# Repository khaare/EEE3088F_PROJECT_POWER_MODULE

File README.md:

# EEE3088F_PROJECT_POWER_MODULE
Our project involves designing and manufacturing the power module for the MM.  The processor, motherboard, and sensing modules have already been designed, so this directory will specifically focus on the design of four functions of the power module, which are to
handle bidirectional motor control, provide External load switching for the mm, voltage regulation and provide an ON/OFF switch for the robot

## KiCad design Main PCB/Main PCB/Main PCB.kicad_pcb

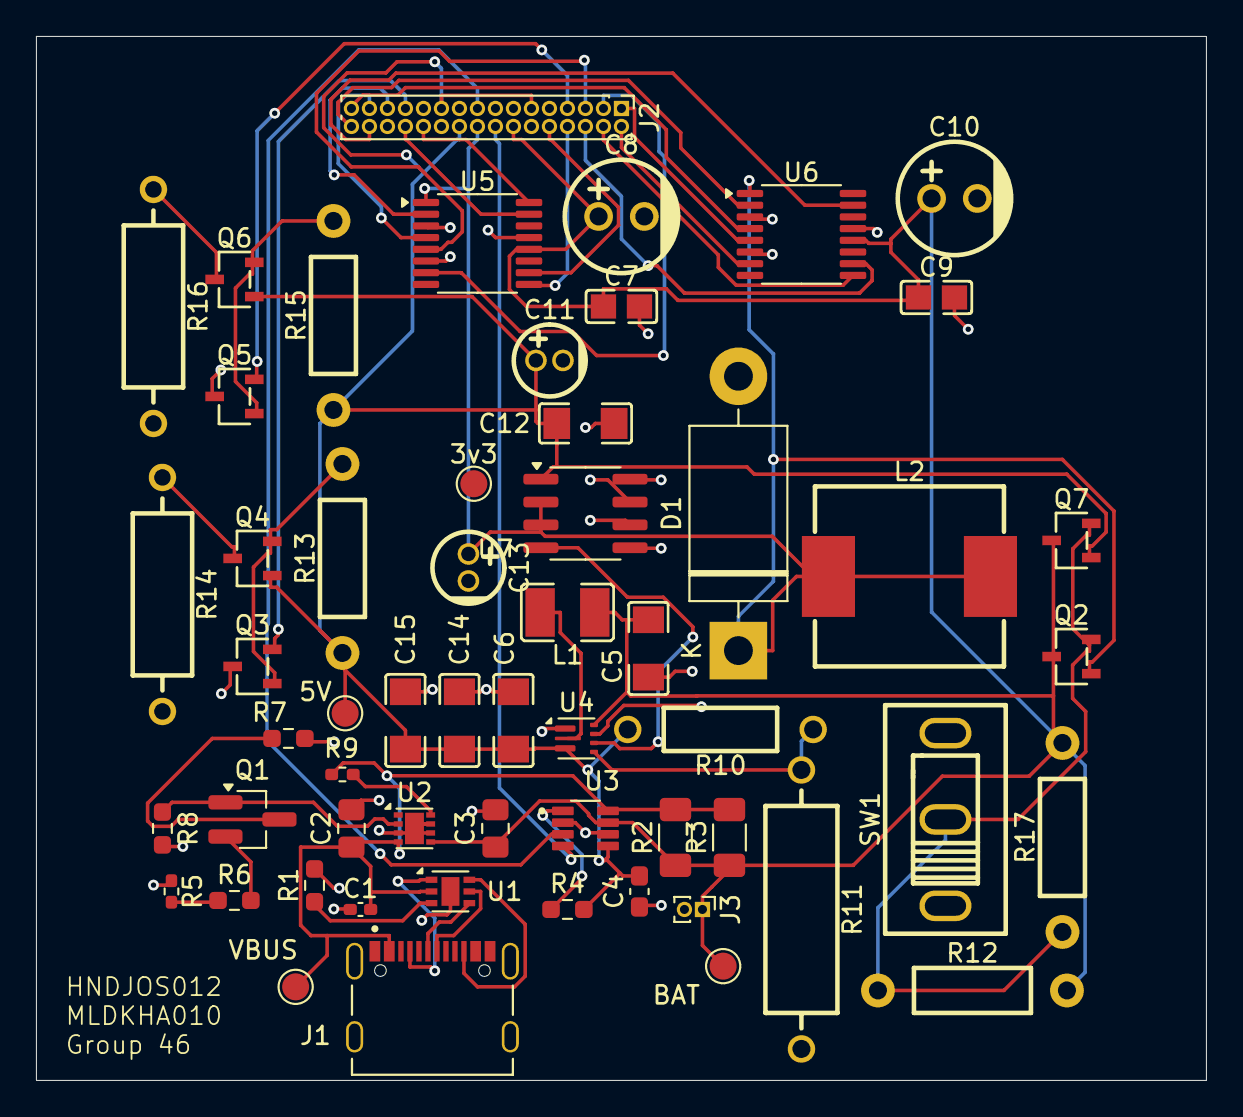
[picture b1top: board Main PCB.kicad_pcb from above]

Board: 2 copper layers, 65.0 x 58.0 mm, 57 parts (0 on the bottom side), 43 nets.

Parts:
3v3, 5V: TestPoint_Pad_D1.5mm
BAT: TestPoint_Pad_D1.5mm
C1: 1uF; C_0402_1005Metric_Pad0.74x0.62mm_HandSolder
C2, C3: 10uF; C_0805_2012Metric_Pad1.18x1.45mm_HandSolder
C4: 100n; C_0603_1608Metric_Pad1.08x0.95mm_HandSolder
C5: 10uF; C1206
C6, C14, C15: 22uF; C1206
C7, C9: 0.01uF; C0805
C8, C10: 10uF; CAP-TH_BD6.3-P2.50-D1.0-FD
C11, C13: 22uF; CAP-TH_BD4.0-P1.50-D0.8-FD
C12: 0.1uF; C1206
D1: 1N5820; D_DO-201AD_P15.24mm_Horizontal
J1: USB_C_Receptacle_USB2.0_16P; SHOUHAN_TYPE-C_16PIN_2MD__073_
J2: Conn_02x16_Odd_Even; PinHeader_2x16_P1.00mm_Vertical
J3: Conn_01x02_Pin; PinHeader_1x02_P1.00mm_Vertical
L1: 1uH; IND-SMD_L3.2-W2.5_L3225
L2: 47uH; IND-SMD_L10.5-W10.0
Q1: NMOS; SOT-23_Handsoldering
Q2, Q4, Q6, Q7: PMOS; SOT-23-3_L3.0-W1.7-P0.95-LS2.9-BR
Q3, Q5: NMOS; SOT-23-3_L3.0-W1.7-P0.95-LS2.9-BR
R1: 75k; R_0603_1608Metric_Pad0.98x0.95mm_HandSolder
R2, R3: 100m; R_1206_3216Metric_Pad1.30x1.75mm_HandSolder
R4: 3.3k; R_0603_1608Metric_Pad0.98x0.95mm_HandSolder
R5, R9: 100k; R_0402_1005Metric_Pad0.72x0.64mm_HandSolder
R6: 10k; R_0603_1608Metric_Pad0.98x0.95mm_HandSolder
R7: 2.4k; R_0603_1608Metric_Pad0.98x0.95mm_HandSolder
R8: 5.1k; R_0603_1608Metric_Pad0.98x0.95mm_HandSolder
R10: 750k; RES-TH_BD2.4-L6.3-P10.30-D0.6
R11: 100k; RES-TH_BD4.0-L11.5-P15.50-D0.7
R12, R13, R15, R17: 10k; RES-TH_BD2.5-L6.5-P10.50-D0.6
R14, R16: 100; RES-TH_BD3.3-L9.0-P13.00-D0.6
SW1: SW_Nidec_CAS-120A1; SW-TH_SHOU-HAN_SS12D10G4
U1: DFN-6L-EP(2x2)_USB_PD_ROHS; DFN-6-1EP_2x2mm_P0.65mm_EP1x1.6mm
U2: DFN-8-EP(2x2) Battery Management ROHS; DFN-8-1EP_2x2mm_P0.5mm_EP1.05x1.75mm
U3: INA219AxD; SOT65P280X145-8N
U4: TPS61022; Texas_RWU0007A_VQFN-7_2x2mm_P0.5mm
U5, U6: DRV8833PW; TSSOP-16_4.4x5mm_P0.65mm
U7: XL1509-3.3; SOIC-8_3.9x4.9mm_P1.27mm
VBUS: TestPoint_Pad_D1.5mm

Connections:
/3v3: 3v3.1, C13.1, D1.1 (K), J2.18, L2.1, L2.2, Q2.1 (D), U5.1 (~SLEEP), U6.1 (~SLEEP), U7.2 (OUT), U7.3 (FB)
/5V: 5V.1, C4.2, C6.1, C11.1, C12.1, C14.1, C15.1, J2.11, J2.20, J2.21, Q4.1 (D), Q6.1 (D), Q7.1 (D), R4.2, R10.1, R13.1, R15.1, U3.5 (VS), U4.3 (VOUT), U7.1 (VIN)
/BAT: BAT.1, C3.1, C5.1, C7.1, C8.1, C9.1, C10.1, J2.14, J3.1, L1.1, Q2.3 (S), Q7.3 (S), R2.1, R3.1, R12.2, R17.2, U2.5 (BAT), U3.7 (IN-), U4.7 (VIN), U5.12 (VM), U6.12 (VM)
/CC1: J1.A5 (CC1), U1.1 (CC1)
/CC2: J1.B5 (CC2), U1.6 (CC2)
/D+: J1.A6 (D+), U1.4 (D+)
/D-: J1.A7 (D-), U1.5 (D-)
/Pin 1: J2.1, U6.5 (BOUT2)
/Pin 2: J2.2, U6.7 (BOUT1)
/Pin 3: J2.3, U5.7 (BOUT1)
/Pin 4: J2.4, U6.9 (BIN1)
/Pin 5: J2.5, U5.5 (BOUT2)
/Pin 6: J2.6, U6.10 (BIN2)
/Pin 7: J2.7, Q5.2 (G)
/Pin 8: J2.8, U5.9 (BIN1)
/Pin 10: J2.10, U5.10 (BIN2)
/Pin 13: R5.2, R6.1
/Pin 16: J2.16, U3.4 (SCL)
/Pin 17: J2.17, U3.3 (SDA)
/Pin 24: J2.24, U5.16 (AIN1)
/Pin 25: J2.25, Q3.2 (G)
/Pin 26: J2.26, U5.15 (AIN2)
/Pin 27: J2.27, U5.2 (AOUT1)
/Pin 29: J2.29, U5.4 (AOUT2)
/Pin 30: J2.30, U6.15 (AIN2)
/Pin 31: J2.31, U6.4 (AOUT2)
/Pin 32: J2.32, U6.2 (AOUT1)
/SWITCH_OUT: U4.5 (EN), U7.4 (~EN)
/VBUS: C1.2, C2.1, R2.2, R3.2, R9.1, U1.2 (VBUS), U2.4 (VCC), U3.8 (IN+), VBUS.1
GND: C1.1, C2.2, C3.2, C4.1, C5.2, C6.2, C7.2, C8.2, C9.2, C10.2, C11.2, C12.2, C13.2, C14.2, C15.2, D1.2 (A), J2.19, J2.23, J3.2, Q3.3 (S), Q5.3 (S), R1.2, R5.1, R7.2, R8.2, R11.2, R14.2, R16.2, SW1.1 (C), U1.7 (GND), U2.1 (TS), U2.3 (GND), U2.6 (STBY), U2.7 (CHRG), U2.9 (EP), U3.2 (A0), U3.6 (GND), U4.1 (GND), U4.6 (MODE), U5.3 (AISEN), U5.6 (BISEN), U5.13 (GND), U6.3 (AISEN), U6.6 (BISEN), U6.13 (GND), U7.5 (GND), U7.6 (GND), U7.7 (GND), U7.8 (GND)
unnamed: Q1.1 (D), R8.1, U2.2 (PROG)
unnamed: Q1.2 (G), R6.2
unnamed: Q1.3 (S), R7.1
unnamed: Q2.2 (G), Q7.2 (G), R12.1, R17.1, SW1.2 (B)
unnamed: Q3.1 (D), Q4.2 (G), R13.2
unnamed: Q4.3 (S), R14.1
unnamed: Q5.1 (D), Q6.2 (G), R15.2
unnamed: Q6.3 (S), R16.1
unnamed: R1.1, U1.3 (VSET)
unnamed: R9.2, U2.8 (CE)
unnamed: R4.1, U3.1 (A1)
unnamed: R10.2, R11.1, U4.4 (FB)
unnamed: L1.2, U4.2 (SW)

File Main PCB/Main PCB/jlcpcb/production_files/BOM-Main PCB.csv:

Comment,Designator,Footprint,LCSC,Quantity
100n,C4,C_0603_1608Metric_Pad1.08x0.95mm_HandSolder,C14663,1
10uF,"C2,C3",C_0805_2012Metric_Pad1.18x1.45mm_HandSolder,C15850,2
DFN-6L-EP(2x2)_USB_PD_ROHS,U1,DFN-6-1EP_2x2mm_P0.65mm_EP1x1.6mm,C22373734,1
2.4k,R7,R_0603_1608Metric_Pad0.98x0.95mm_HandSolder,C22940,1
3.3k,R4,R_0603_1608Metric_Pad0.98x0.95mm_HandSolder,C22978,1
5.1k,R8,R_0603_1608Metric_Pad0.98x0.95mm_HandSolder,C23186,1
75k,R1,R_0603_1608Metric_Pad0.98x0.95mm_HandSolder,C23242,1
100m,"R2,R3",R_1206_3216Metric_Pad1.30x1.75mm_HandSolder,C25334,2
100k,"R5,R9",R_0402_1005Metric_Pad0.72x0.64mm_HandSolder,C25741,2
10k,R6,R_0603_1608Metric_Pad0.98x0.95mm_HandSolder,C25804,1
DFN-8-EP(2x2) Battery Management ROHS,U2,DFN-8-1EP_2x2mm_P0.5mm_EP1.05x1.75mm,C2974724,1
USB_C_Receptacle_USB2.0_16P,J1,SHOUHAN_TYPE-C_16PIN_2MD__073_,C393939,1
1uF,C1,C_0402_1005Metric_Pad0.74x0.62mm_HandSolder,C52923,1
NMOS,Q1,SOT-23_Handsoldering,C8545,1
INA219AxD,U3,SOT65P280X145-8N,C87469,1
0.01uF,C7,C0805,,1
SW_Nidec_CAS-120A1,SW1,SW-TH_SHOU-HAN_SS12D10G4,,1
XL1509-3.3,U7,SOIC-8_3.9x4.9mm_P1.27mm,,1
22uF,C14,C1206,,1
PMOS,Q4,SOT-23-3_L2.9-W1.3-P1.90-LS2.4-BR,,1
PMOS,Q6,SOT-23-3_L2.9-W1.3-P1.90-LS2.4-BR,,1
TPS61022,U4,Texas_RWU0007A_VQFN-7_2x2mm_P0.5mm,,1
NMOS,Q5,SOT-23-3_L2.9-W1.6-P1.90-LS2.8-BR,,1
10uF,C10,CAP-TH_BD6.3-P2.50-D1.0-FD,,1
22uF,C13,CAP-TH_BD4.0-P1.50-D0.8-FD,,1
PMOS,Q7,SOT-23-3_L2.9-W1.3-P1.90-LS2.4-BR,,1
22uF,C6,C1206,,1
PMOS,Q2,SOT-23-3_L2.9-W1.3-P1.90-LS2.4-BR,,1
1uH,L1,IND-SMD_L3.2-W2.5_L3225,,1
100k,R11,RES-TH_BD4.0-L11.5-P15.50-D0.7,,1
10uF,C5,C1206,,1
10k,R17,RES-TH_BD2.5-L6.5-P10.50-D0.6,,1
NMOS,Q3,SOT-23-3_L2.9-W1.6-P1.90-LS2.8-BR,,1
22uF,C11,CAP-TH_BD4.0-P1.50-D0.8-FD,,1
100,R14,RES-TH_BD3.3-L9.0-P13.00-D0.6,,1
DRV8833PW,U5,TSSOP-16_4.4x5mm_P0.65mm,,1
DRV8833PW,U6,TSSOP-16_4.4x5mm_P0.65mm,,1
0.1uF,C12,C1206,,1
10k,R12,RES-TH_BD2.5-L6.5-P10.50-D0.6,,1
47uH,L2,IND-SMD_L10.5-W10.0,,1
100,R16,RES-TH_BD3.3-L9.0-P13.00-D0.6,,1
10uF,C8,CAP-TH_BD6.3-P2.50-D1.0-FD,,1
750k,R10,RES-TH_BD2.4-L6.3-P10.30-D0.6,,1
0.01uF,C9,C0805,,1
10k,R15,RES-TH_BD2.5-L6.5-P10.50-D0.6,,1
10k,R13,RES-TH_BD2.5-L6.5-P10.50-D0.6,,1
1N5820,D1,D_DO-201AD_P15.24mm_Horizontal,,1
22uF,C15,C1206,,1

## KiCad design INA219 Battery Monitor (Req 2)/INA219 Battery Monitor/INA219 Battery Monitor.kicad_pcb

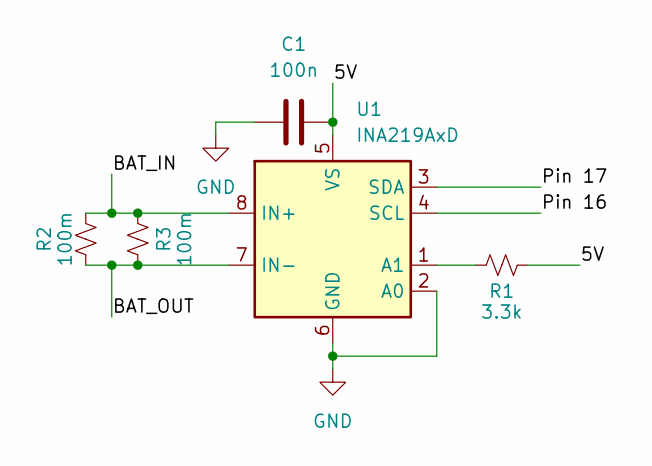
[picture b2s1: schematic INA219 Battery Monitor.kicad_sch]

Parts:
C1: 100n; C_0603_1608Metric_Pad1.08x0.95mm_HandSolder; JLCPCB Part # C14663
R1: 3.3k; R_0603_1608Metric_Pad0.98x0.95mm_HandSolder; JLCPCB Part # C22978
R2, R3: 100m; R_1206_3216Metric_Pad1.30x1.75mm_HandSolder; JLCPCB # C25334
U1: INA219AxD; SOT65P280X145-8N; JLCPCB Part # C87469

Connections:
/5V: C1.2, R1.2, U1.5 (VS)
/BAT_IN: R2.2, R3.2, U1.8 (IN+)
/BAT_OUT: R2.1, R3.1, U1.7 (IN-)
/Pin 16: U1.4 (SCL)
/Pin 17: U1.3 (SDA)
GND: C1.1, U1.2 (A0), U1.6 (GND)
unnamed: R1.1, U1.1 (A1)

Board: 2 copper layers, 5 parts (0 on the bottom side), 5 nets, no tracks yet.

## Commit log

2025-03-21 proj_des
2025-03-21 Design Files Updated
2025-03-21 Added Schematic and PCB Files
2025-03-21 Updated Charging and Charge Mode Design Documents
2025-03-21 Create Motors
2025-03-21 Create overview..
2025-03-21 Create file1
2025-03-21 Create file
2025-03-21 Create file2
2025-03-21 Create file3
2025-03-21 Update file2
2025-03-22 Req 3 & 4 Circuit Created
    Merged requirements 3 and 4, updated design documents, and created KiCad circuit.
2025-03-23 Update file3
2025-03-24 Added Component Part Numbers
2025-03-25 Created INA219 Schematic and PCB
2025-03-25 Update Footprints
2025-03-26 Updated Footprints
2025-03-26 Moved Files and Created Main PCB Project
2025-03-26 Updated Footprints and Added Joshua's Requirements to Main PCB
2025-03-26 Updated Main PCB
2025-03-27 Updated Pin Connections
2025-03-27 Created Main PCB First Draft
2025-03-28 Finalized Main PCB and Generated Gerbers
2025-03-28 Updated Footprints and Added First Submission Files
2025-05-16 Create Project descriptions (V1-V4)
2025-05-16 Create new folder
2025-05-16 Rename [OUTDATED] EEE3088F 2025 Project Description v1.pdf to Project description (V1-V4)/[OUTDATED] EEE3088F 2025 Project Description v1.pdf
2025-05-16 Rename [OUTDATED] EEE3088F_2025_project_description_v2.pdf to Project description (V1-V4)/[OUTDATED] EEE3088F_2025_project_description_v2.pdf
2025-05-16 Rename [OUTDATED] EEE3088F_2025_project_description_v3.pdf to Project description (V1-V4)/[OUTDATED] EEE3088F_2025_project_description_v3.pdf
2025-05-16 Rename EEE3088F_2025_project_description_v4.pdf to Project description (V1-V4)/EEE3088F_2025_project_description_v4.pdf
